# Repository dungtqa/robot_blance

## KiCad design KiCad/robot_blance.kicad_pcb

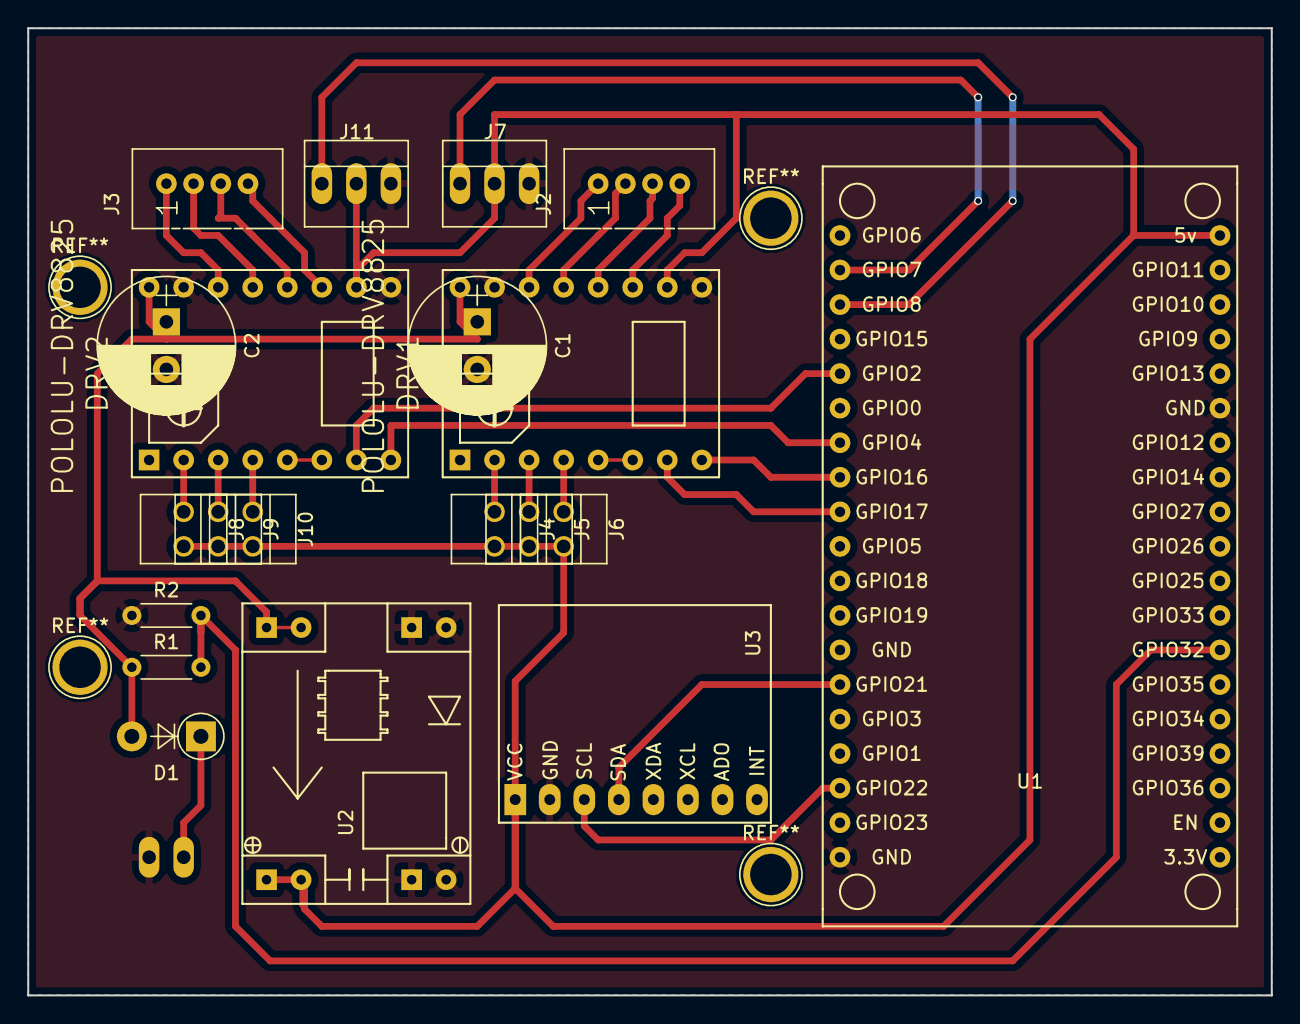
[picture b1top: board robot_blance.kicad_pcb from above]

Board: 2 copper layers, 91.4 x 71.1 mm, 21 parts (1 on the bottom side), 29 nets.

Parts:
C1, C2: CP1; CP_Radial_D10.0mm_P3.50mm
D1: D; D_DO-41_SOD81_P5.08mm_Vertical_AnodeUp
DRV1, DRV2: POLOLU-DRV8825
J1: Bat; PINHEAD1-2
J2, J3: CONN_01X04; Grove_1x04
J4, J5, J6, J8, J9, J10: CONN_01X02; PINHEAD1-2
J7, J11: CONN_01X03; PINHEAD1-3
R1, R2: R; R_Axial_DIN0204_L3.6mm_D1.6mm_P5.08mm_Horizontal
U1: Esp32Dev
U2: MP1584; MP1584_buck_module
U3: MPU6050

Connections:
+5V: DRV1.10, DRV2.10, J4.2, J5.2, J6.2, J7.2, J8.2, J9.2, J10.2, J11.2, U1.1, U2.4, U3.1
+12V: D1.1, J1.1
GND: C1.2, C2.2, DRV1.9, DRV1.15, DRV2.9, DRV2.15, J1.2, J7.3, J11.3, R2.1, U1.6, U1.20, U2.2, U2.3, U3.2
unnamed: C1.1, C2.1, D1.2, DRV1.16, DRV2.16, R1.1, U2.1
unnamed: DRV1.2, J4.1
unnamed: DRV1.3, J5.1
unnamed: DRV1.4, J6.1
unnamed: DRV1.5, DRV1.6
unnamed: DRV1.7, U1.30
unnamed: DRV1.8, U1.31
unnamed: DRV1.11, J2.4
unnamed: DRV1.12, J2.3
unnamed: DRV1.13, J2.2
unnamed: DRV1.14, J2.1
unnamed: DRV2.2, J8.1
unnamed: DRV2.3, J9.1
unnamed: DRV2.4, J10.1
unnamed: DRV2.5, DRV2.6
unnamed: DRV2.7, U1.34
unnamed: DRV2.8, U1.32
unnamed: DRV2.11, J3.4
unnamed: DRV2.12, J3.3
unnamed: DRV2.13, J3.2
unnamed: DRV2.14, J3.1
unnamed: J7.1, U1.37
unnamed: J11.1, U1.36
unnamed: R1.2, R2.2, U1.13
unnamed: U1.22, U3.3
unnamed: U1.25, U3.4

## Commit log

2018-01-03 Init
2018-01-04 Stepper
2018-01-12 Add components
2018-01-14 Servo
2018-01-15 Router
2018-01-23 Gbert
2018-09-18 mqtt
